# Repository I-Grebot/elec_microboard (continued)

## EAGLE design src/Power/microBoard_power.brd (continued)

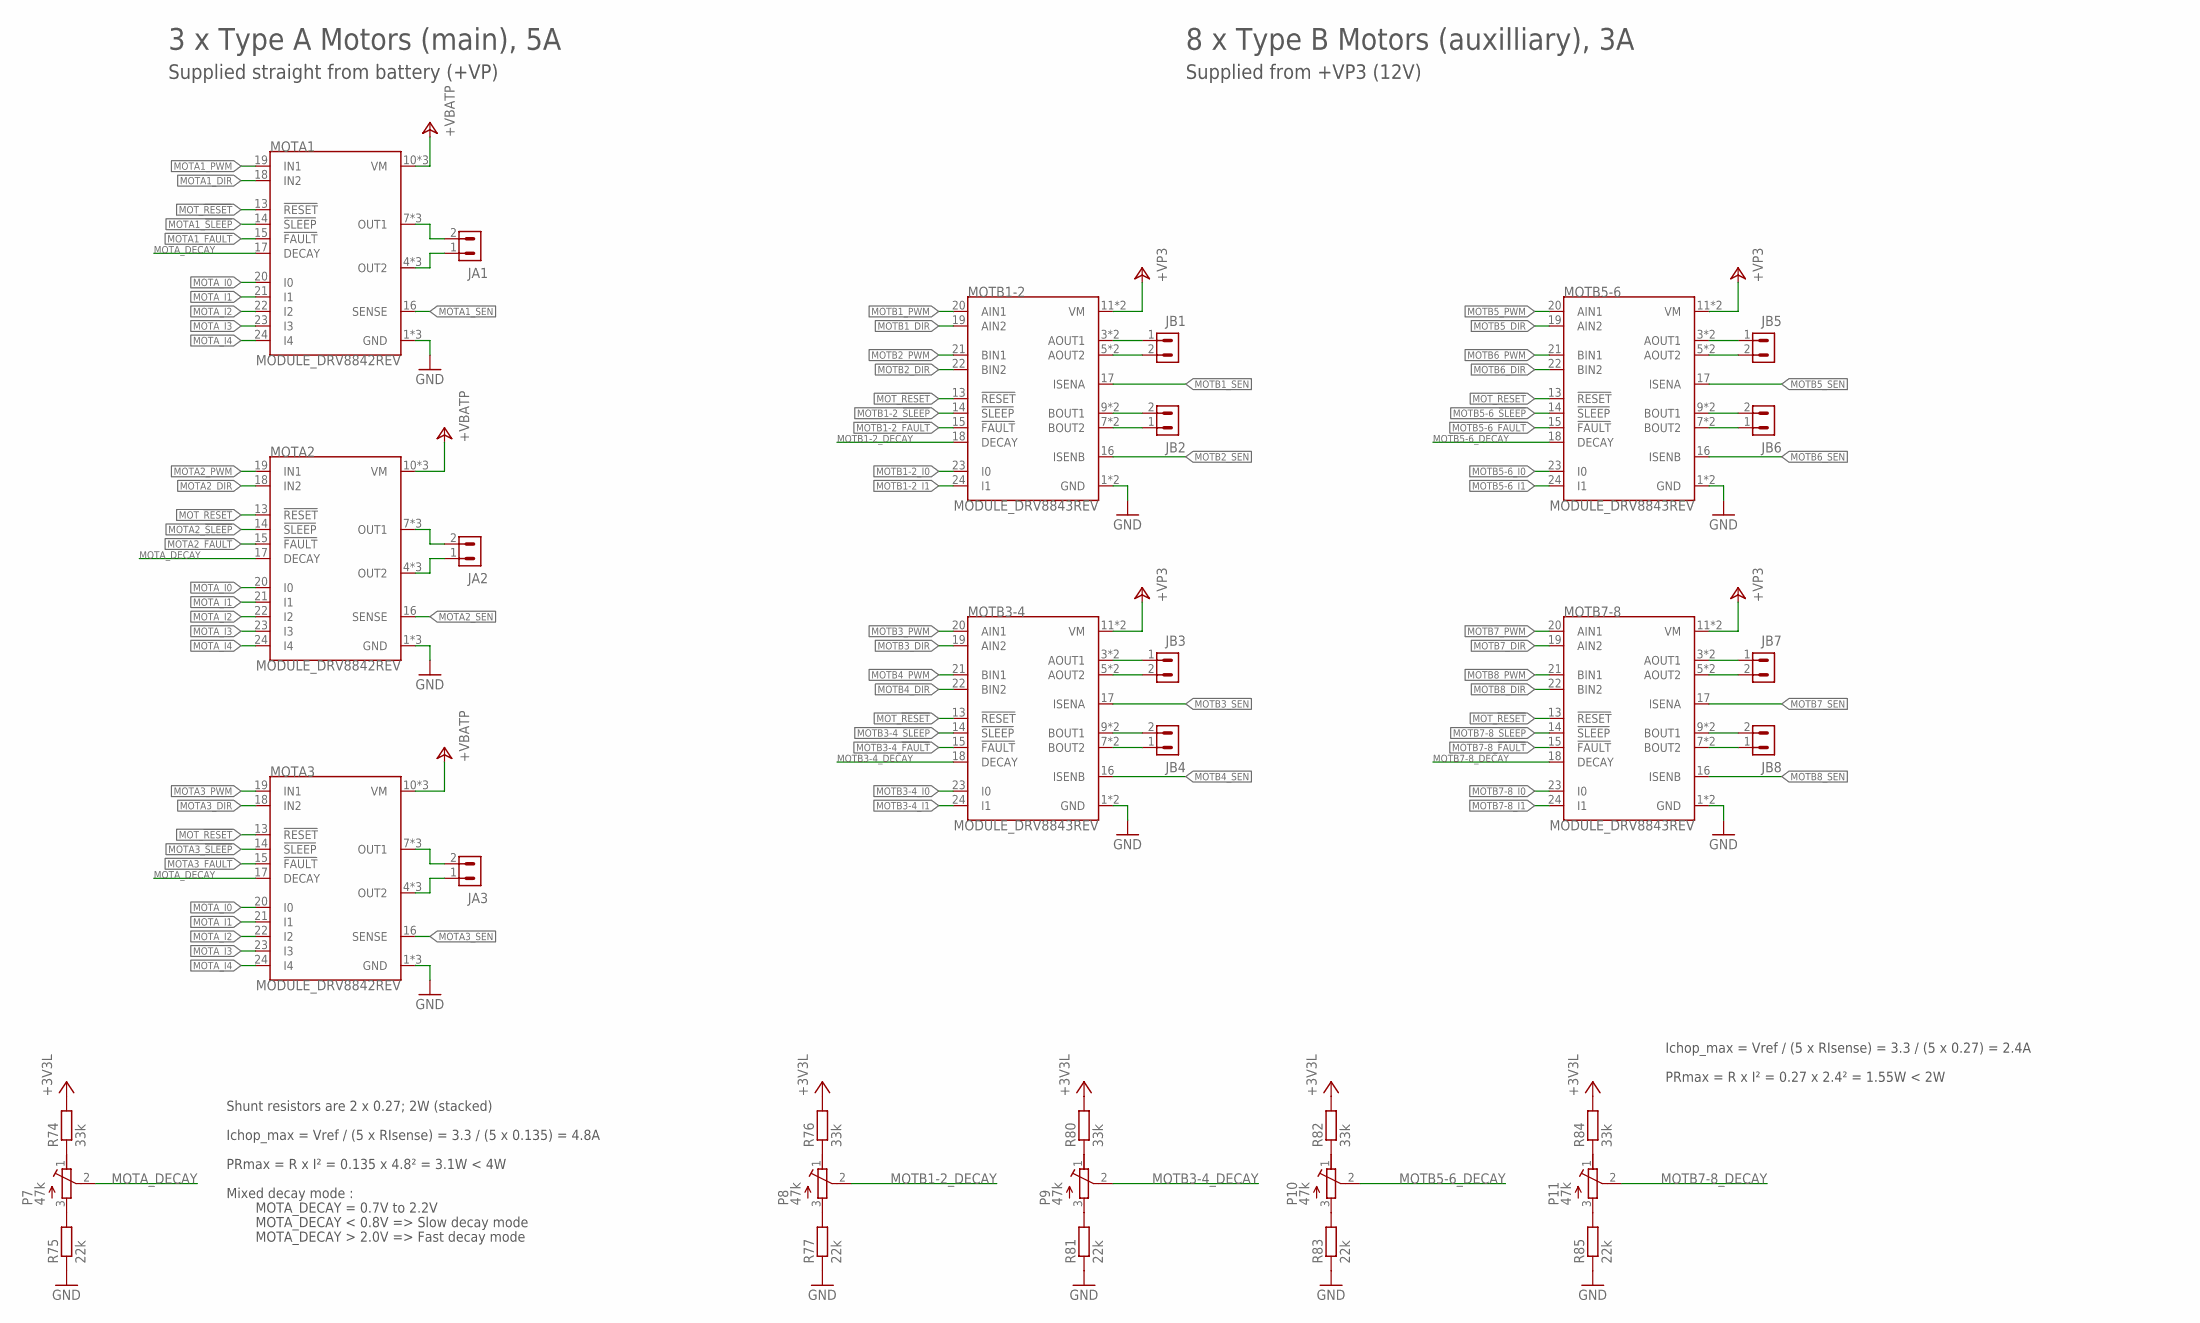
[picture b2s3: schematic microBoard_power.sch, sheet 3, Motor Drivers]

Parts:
JA1, JA2, JA3: MC15-G-3-3.81_2; CON_3.81_2
JB1, JB2, JB3, JB4, JB5, JB6, JB7, JB8: MC15-G-3-3.81_2; CON_3.81_2
MOTA1, MOTA2, MOTA3: MODULE_DRV8842REV; MODULE_DRV884X_REV
MOTB1-2, MOTB3-4, MOTB5-6, MOTB7-8: MODULE_DRV8843REV; MODULE_DRV884X_REV
P7, P8, P9, P10, P11: 47k; RTRIMT93XB
R74, R76, R80, R82, R84: 33k; R0603
R75, R77, R81, R83, R85: 22k; R0603

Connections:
+3V3L: R74.2, R76.2, R80.2, R82.2, R84.2; also elsewhere on the board
+VBATP: MOTA1.10 (VM), MOTA1.11 (VM), MOTA1.12 (VM), MOTA2.10 (VM), MOTA2.11 (VM), MOTA2.12 (VM), MOTA3.10 (VM), MOTA3.11 (VM), MOTA3.12 (VM); also elsewhere on the board
+VP3: MOTB1-2.11 (VM), MOTB1-2.12 (VM), MOTB3-4.11 (VM), MOTB3-4.12 (VM), MOTB5-6.11 (VM), MOTB5-6.12 (VM), MOTB7-8.11 (VM), MOTB7-8.12 (VM); also elsewhere on the board
GND: MOTA1.1 (GND), MOTA1.2 (GND), MOTA1.3 (GND), MOTA2.1 (GND), MOTA2.2 (GND), MOTA2.3 (GND), MOTA3.1 (GND), MOTA3.2 (GND), MOTA3.3 (GND), MOTB1-2.1 (GND), MOTB1-2.2 (GND), MOTB3-4.1 (GND), MOTB3-4.2 (GND), MOTB5-6.1 (GND), MOTB5-6.2 (GND), MOTB7-8.1 (GND), MOTB7-8.2 (GND), R75.1, R77.1, R81.1, R83.1, R85.1; also elsewhere on the board
MOTA1_!FAULT!: MOTA1.15 (!FAULT!); also elsewhere on the board
MOTA1_!SLEEP!: MOTA1.14 (!SLEEP!); also elsewhere on the board
MOTA1_DIR: MOTA1.18 (IN2); also elsewhere on the board
MOTA1_PWM: MOTA1.19 (IN1); also elsewhere on the board
MOTA1_SEN: MOTA1.16 (SENSE); also elsewhere on the board
MOTA2_!FAULT!: MOTA2.15 (!FAULT!); also elsewhere on the board
MOTA2_!SLEEP!: MOTA2.14 (!SLEEP!); also elsewhere on the board
MOTA2_DIR: MOTA2.18 (IN2); also elsewhere on the board
MOTA2_PWM: MOTA2.19 (IN1); also elsewhere on the board
MOTA2_SEN: MOTA2.16 (SENSE); also elsewhere on the board
MOTA3_!FAULT!: MOTA3.15 (!FAULT!); also elsewhere on the board
MOTA3_!SLEEP!: MOTA3.14 (!SLEEP!); also elsewhere on the board
MOTA3_DIR: MOTA3.18 (IN2); also elsewhere on the board
MOTA3_PWM: MOTA3.19 (IN1); also elsewhere on the board
MOTA3_SEN: MOTA3.16 (SENSE); also elsewhere on the board
MOTA_DECAY: MOTA1.17 (DECAY), MOTA2.17 (DECAY), MOTA3.17 (DECAY), P7.2 (S)
MOTA_I0: MOTA1.20 (I0), MOTA2.20 (I0), MOTA3.20 (I0); also elsewhere on the board
MOTA_I1: MOTA1.21 (I1), MOTA2.21 (I1), MOTA3.21 (I1); also elsewhere on the board
MOTA_I2: MOTA1.22 (I2), MOTA2.22 (I2), MOTA3.22 (I2); also elsewhere on the board
MOTA_I3: MOTA1.23 (I3), MOTA2.23 (I3), MOTA3.23 (I3); also elsewhere on the board
MOTA_I4: MOTA1.24 (I4), MOTA2.24 (I4), MOTA3.24 (I4); also elsewhere on the board
MOTB1-2_!FAULT!: MOTB1-2.15 (!FAULT!); also elsewhere on the board
MOTB1-2_!SLEEP!: MOTB1-2.14 (!SLEEP!); also elsewhere on the board
MOTB1-2_DECAY: MOTB1-2.18 (DECAY), P8.2 (S)
MOTB1-2_I0: MOTB1-2.23 (I0); also elsewhere on the board
MOTB1-2_I1: MOTB1-2.24 (I1); also elsewhere on the board
MOTB1_DIR: MOTB1-2.19 (AIN2); also elsewhere on the board
MOTB1_PWM: MOTB1-2.20 (AIN1); also elsewhere on the board
MOTB1_SEN: MOTB1-2.17 (ISENA); also elsewhere on the board
MOTB2_DIR: MOTB1-2.22 (BIN2); also elsewhere on the board
MOTB2_PWM: MOTB1-2.21 (BIN1); also elsewhere on the board
MOTB2_SEN: MOTB1-2.16 (ISENB); also elsewhere on the board
MOTB3-4_!FAULT!: MOTB3-4.15 (!FAULT!); also elsewhere on the board
MOTB3-4_!SLEEP!: MOTB3-4.14 (!SLEEP!); also elsewhere on the board
MOTB3-4_DECAY: MOTB3-4.18 (DECAY), P9.2 (S)
MOTB3-4_I0: MOTB3-4.23 (I0); also elsewhere on the board
MOTB3-4_I1: MOTB3-4.24 (I1); also elsewhere on the board
MOTB3_DIR: MOTB3-4.19 (AIN2); also elsewhere on the board
MOTB3_PWM: MOTB3-4.20 (AIN1); also elsewhere on the board
MOTB3_SEN: MOTB3-4.17 (ISENA); also elsewhere on the board
MOTB4_DIR: MOTB3-4.22 (BIN2); also elsewhere on the board
MOTB4_PWM: MOTB3-4.21 (BIN1); also elsewhere on the board
MOTB4_SEN: MOTB3-4.16 (ISENB); also elsewhere on the board
MOTB5-6_!FAULT!: MOTB5-6.15 (!FAULT!); also elsewhere on the board
MOTB5-6_!SLEEP!: MOTB5-6.14 (!SLEEP!); also elsewhere on the board
MOTB5-6_DECAY: MOTB5-6.18 (DECAY), P10.2 (S)
MOTB5-6_I0: MOTB5-6.23 (I0); also elsewhere on the board
MOTB5-6_I1: MOTB5-6.24 (I1); also elsewhere on the board
MOTB5_DIR: MOTB5-6.19 (AIN2); also elsewhere on the board
MOTB5_PWM: MOTB5-6.20 (AIN1); also elsewhere on the board
MOTB5_SEN: MOTB5-6.17 (ISENA); also elsewhere on the board
MOTB6_DIR: MOTB5-6.22 (BIN2); also elsewhere on the board
MOTB6_PWM: MOTB5-6.21 (BIN1); also elsewhere on the board
MOTB6_SEN: MOTB5-6.16 (ISENB); also elsewhere on the board
MOTB7-8_!FAULT!: MOTB7-8.15 (!FAULT!); also elsewhere on the board
MOTB7-8_!SLEEP!: MOTB7-8.14 (!SLEEP!); also elsewhere on the board
MOTB7-8_DECAY: MOTB7-8.18 (DECAY), P11.2 (S)
MOTB7-8_I0: MOTB7-8.23 (I0); also elsewhere on the board
MOTB7-8_I1: MOTB7-8.24 (I1); also elsewhere on the board
MOTB7_DIR: MOTB7-8.19 (AIN2); also elsewhere on the board
MOTB7_PWM: MOTB7-8.20 (AIN1); also elsewhere on the board
MOTB7_SEN: MOTB7-8.17 (ISENA); also elsewhere on the board
MOTB8_DIR: MOTB7-8.22 (BIN2); also elsewhere on the board
MOTB8_PWM: MOTB7-8.21 (BIN1); also elsewhere on the board
MOTB8_SEN: MOTB7-8.16 (ISENB); also elsewhere on the board
MOT_!RESET!: MOTA1.13 (!RESET!), MOTA2.13 (!RESET!), MOTA3.13 (!RESET!), MOTB1-2.13 (!RESET!), MOTB3-4.13 (!RESET!), MOTB5-6.13 (!RESET!), MOTB7-8.13 (!RESET!); also elsewhere on the board
unnamed: JA1.2, MOTA1.7 (OUT1), MOTA1.8 (OUT1), MOTA1.9 (OUT1)
unnamed: JA2.2, MOTA2.7 (OUT1), MOTA2.8 (OUT1), MOTA2.9 (OUT1)
unnamed: JB3.1, MOTB3-4.3 (AOUT1), MOTB3-4.4 (AOUT1)
unnamed: JB3.2, MOTB3-4.5 (AOUT2), MOTB3-4.6 (AOUT2)
unnamed: JB4.1, MOTB3-4.7 (BOUT2), MOTB3-4.8 (BOUT2)
unnamed: JA2.1, MOTA2.4 (OUT2), MOTA2.5 (OUT2), MOTA2.6 (OUT2)
unnamed: JA1.1, MOTA1.4 (OUT2), MOTA1.5 (OUT2), MOTA1.6 (OUT2)
unnamed: JB1.1, MOTB1-2.3 (AOUT1), MOTB1-2.4 (AOUT1)
unnamed: JB1.2, MOTB1-2.5 (AOUT2), MOTB1-2.6 (AOUT2)
unnamed: JB2.2, MOTB1-2.9 (BOUT1), MOTB1-2.10 (BOUT1)
unnamed: JA3.1, MOTA3.4 (OUT2), MOTA3.5 (OUT2), MOTA3.6 (OUT2)
unnamed: JA3.2, MOTA3.7 (OUT1), MOTA3.8 (OUT1), MOTA3.9 (OUT1)
unnamed: JB4.2, MOTB3-4.9 (BOUT1), MOTB3-4.10 (BOUT1)
unnamed: JB5.1, MOTB5-6.3 (AOUT1), MOTB5-6.4 (AOUT1)
unnamed: JB5.2, MOTB5-6.5 (AOUT2), MOTB5-6.6 (AOUT2)
unnamed: JB6.2, MOTB5-6.9 (BOUT1), MOTB5-6.10 (BOUT1)
unnamed: JB2.1, MOTB1-2.7 (BOUT2), MOTB1-2.8 (BOUT2)
unnamed: JB6.1, MOTB5-6.7 (BOUT2), MOTB5-6.8 (BOUT2)
unnamed: JB7.1, MOTB7-8.3 (AOUT1), MOTB7-8.4 (AOUT1)
unnamed: JB7.2, MOTB7-8.5 (AOUT2), MOTB7-8.6 (AOUT2)
unnamed: JB8.2, MOTB7-8.9 (BOUT1), MOTB7-8.10 (BOUT1)
unnamed: JB8.1, MOTB7-8.7 (BOUT2), MOTB7-8.8 (BOUT2)
unnamed: P7.3 (E), R75.2
unnamed: P7.1 (A), R74.1
unnamed: P8.3 (E), R77.2
unnamed: P8.1 (A), R76.1
unnamed: P9.3 (E), R81.2
unnamed: P9.1 (A), R80.1
unnamed: P10.3 (E), R83.2
unnamed: P10.1 (A), R82.1
unnamed: P11.3 (E), R85.2
unnamed: P11.1 (A), R84.1

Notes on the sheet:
3 x Type A Motors (main), 5A
Ichop_max = Vref / (5 x RIsense) = 3.3 / (5 x 0.135) = 4.8A
Ichop_max = Vref / (5 x RIsense) = 3.3 / (5 x 0.27) = 2.4A
PRmax = R x I² = 0.27 x 2.4² = 1.55W < 2W
PRmax = R x I² = 0.135 x 4.8² = 3.1W < 4W
Shunt resistors are 2 x 0.27; 2W (stacked)
8 x Type B Motors (auxilliary), 3A
Supplied straight from battery (+VP)
Supplied from +VP3 (12V)
Mixed decay mode :
MOTA_DECAY = 0.7V to 2.2V
MOTA_DECAY < 0.8V => Slow decay mode
MOTA_DECAY > 2.0V => Fast decay mode

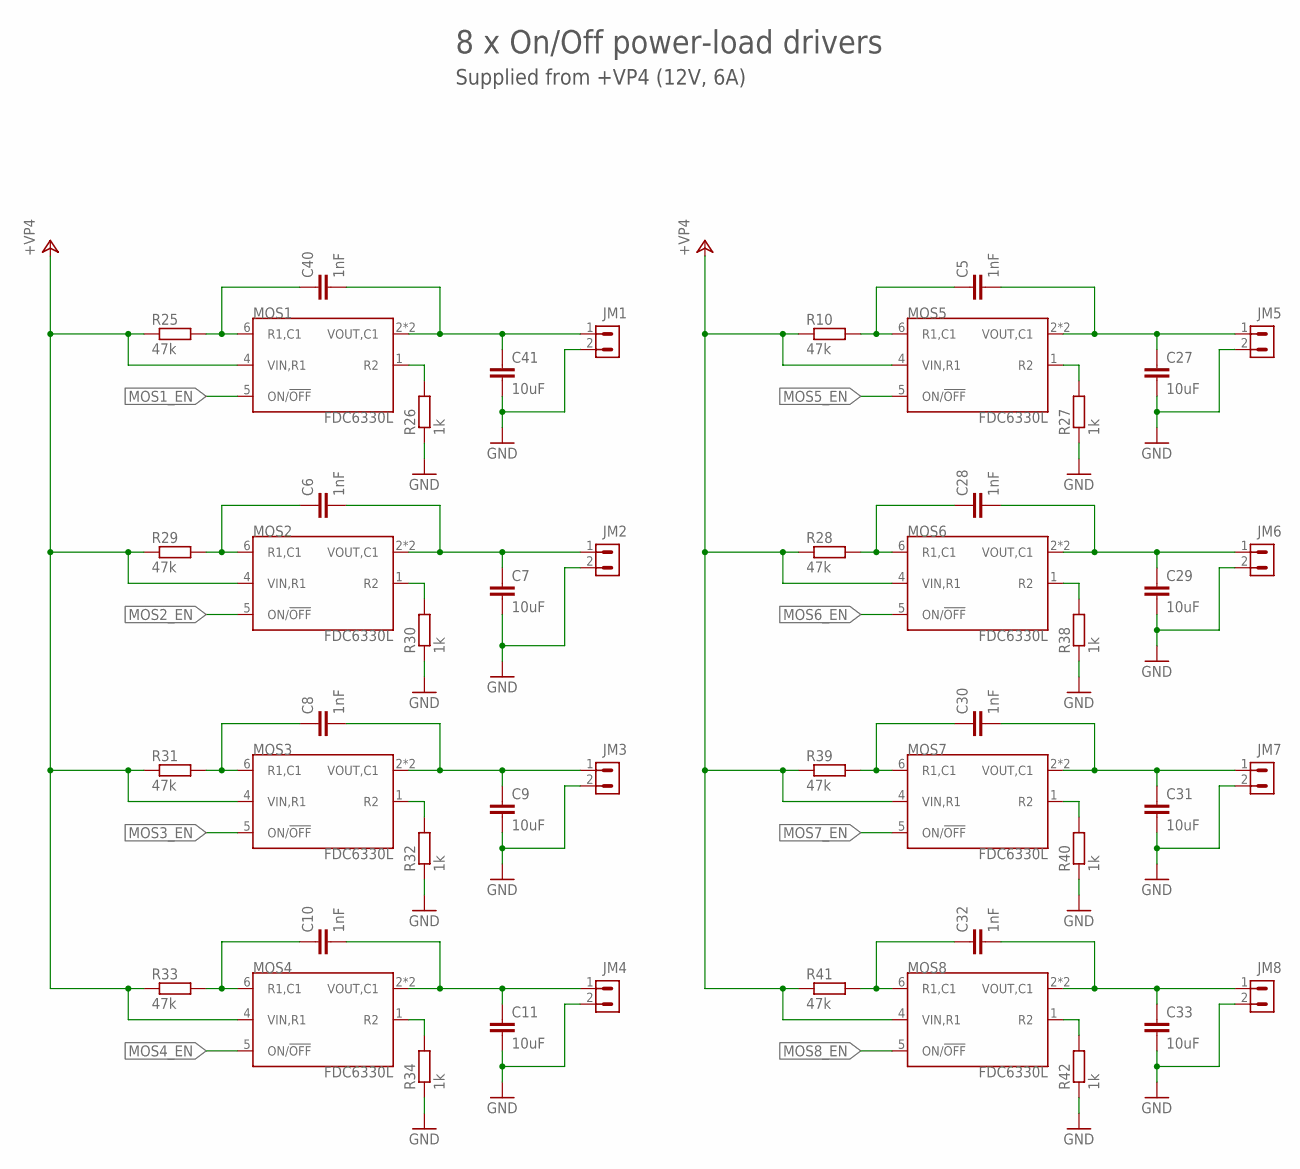
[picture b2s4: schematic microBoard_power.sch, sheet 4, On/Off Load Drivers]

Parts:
C5, C6, C8, C10, C28, C30, C32, C40: 1nF; C0603
C7, C9, C11, C27, C29, C31, C33, C41: 10uF; C1210
JM1, JM2, JM3, JM4, JM5, JM6, JM7, JM8: CON_2.54_H_2
MOS1, MOS2, MOS3, MOS4, MOS5, MOS6, MOS7, MOS8: FDC6330L; SSOT-6
R10, R25, R28, R29, R31, R33, R39, R41: 47k; R0603
R26, R27, R30, R32, R34, R38, R40, R42: 1k; R0603

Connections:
+VP4: MOS1.4 (VIN,R1), MOS2.4 (VIN,R1), MOS3.4 (VIN,R1), MOS4.4 (VIN,R1), MOS5.4 (VIN,R1), MOS6.4 (VIN,R1), MOS7.4 (VIN,R1), MOS8.4 (VIN,R1), R10.1, R25.1, R28.1, R29.1, R31.1, R33.1, R39.1, R41.1; also elsewhere on the board
GND: C7.2, C9.2, C11.2, C27.2, C29.2, C31.2, C33.2, C41.2, JM1.2, JM2.2, JM3.2, JM4.2, JM5.2, JM6.2, JM7.2, JM8.2, R26.1, R27.1, R30.1, R32.1, R34.1, R38.1, R40.1, R42.1; also elsewhere on the board
MOS1_EN: MOS1.5 (ON/!OFF!); also elsewhere on the board
MOS1_OUT: C40.2, C41.1, JM1.1, MOS1.2 (VOUT,C1), MOS1.3 (VOUT,C1)
MOS2_EN: MOS2.5 (ON/!OFF!); also elsewhere on the board
MOS2_OUT: C6.2, C7.1, JM2.1, MOS2.2 (VOUT,C1), MOS2.3 (VOUT,C1)
MOS3_EN: MOS3.5 (ON/!OFF!); also elsewhere on the board
MOS3_OUT: C8.2, C9.1, JM3.1, MOS3.2 (VOUT,C1), MOS3.3 (VOUT,C1)
MOS4_EN: MOS4.5 (ON/!OFF!); also elsewhere on the board
MOS4_OUT: C10.2, C11.1, JM4.1, MOS4.2 (VOUT,C1), MOS4.3 (VOUT,C1)
MOS5_EN: MOS5.5 (ON/!OFF!); also elsewhere on the board
MOS5_OUT: C5.2, C27.1, JM5.1, MOS5.2 (VOUT,C1), MOS5.3 (VOUT,C1)
MOS6_EN: MOS6.5 (ON/!OFF!); also elsewhere on the board
MOS6_OUT: C28.2, C29.1, JM6.1, MOS6.2 (VOUT,C1), MOS6.3 (VOUT,C1)
MOS7_EN: MOS7.5 (ON/!OFF!); also elsewhere on the board
MOS7_OUT: C30.2, C31.1, JM7.1, MOS7.2 (VOUT,C1), MOS7.3 (VOUT,C1)
MOS8_EN: MOS8.5 (ON/!OFF!); also elsewhere on the board
MOS8_OUT: C32.2, C33.1, JM8.1, MOS8.2 (VOUT,C1), MOS8.3 (VOUT,C1)
unnamed: MOS1.1 (R2), R26.2
unnamed: C5.1, MOS5.6 (R1,C1), R10.2
unnamed: C40.1, MOS1.6 (R1,C1), R25.2
unnamed: MOS5.1 (R2), R27.2
unnamed: C28.1, MOS6.6 (R1,C1), R28.2
unnamed: MOS6.1 (R2), R38.2
unnamed: C6.1, MOS2.6 (R1,C1), R29.2
unnamed: MOS2.1 (R2), R30.2
unnamed: C8.1, MOS3.6 (R1,C1), R31.2
unnamed: MOS3.1 (R2), R32.2
unnamed: C10.1, MOS4.6 (R1,C1), R33.2
unnamed: MOS4.1 (R2), R34.2
unnamed: C30.1, MOS7.6 (R1,C1), R39.2
unnamed: MOS7.1 (R2), R40.2
unnamed: C32.1, MOS8.6 (R1,C1), R41.2
unnamed: MOS8.1 (R2), R42.2

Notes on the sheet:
8 x On/Off power-load drivers
Supplied from +VP4 (12V, 6A)

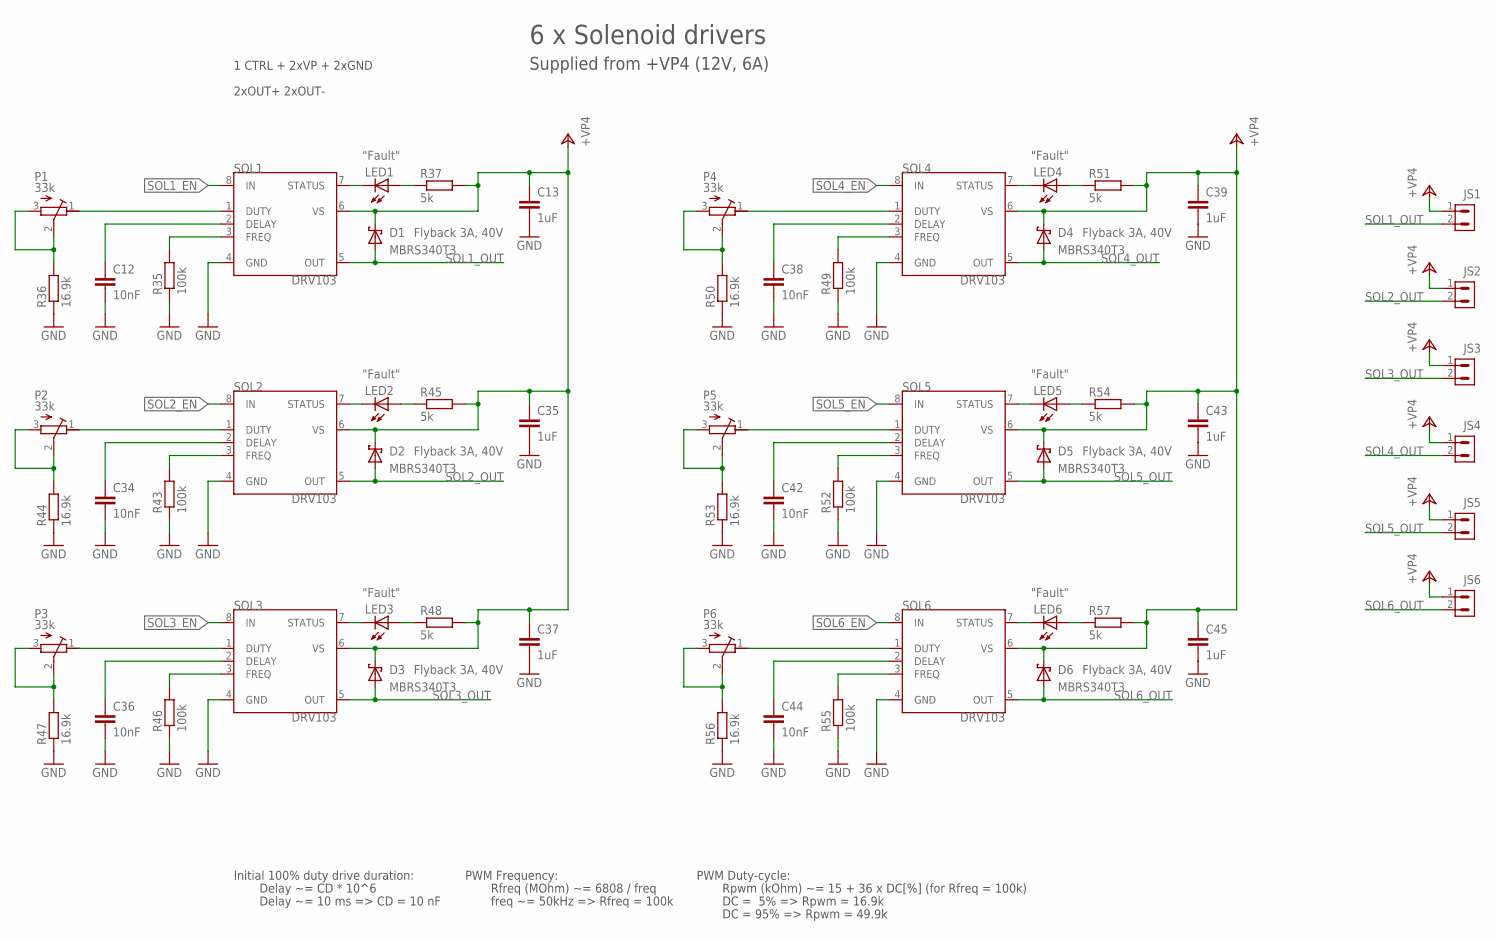
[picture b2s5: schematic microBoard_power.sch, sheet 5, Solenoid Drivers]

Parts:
C12, C34, C36, C38, C42, C44: 10nF; C0603
C13, C35, C37, C39, C43, C45: 1uF; C1210
D1, D2, D3, D4, D5, D6: MBRS340T3; SMC
JS1, JS2, JS3, JS4, JS5, JS6: CON_2.54_H_2
LED1, LED2, LED3, LED4, LED5, LED6: LEDCHIPLED_0805; CHIPLED_0805
P1, P2, P3, P4, P5, P6: 33k; RTRIMT93XB
R35, R43, R46, R49, R52, R55: 100k; R0603
R36, R44, R47, R50, R53, R56: 16.9k; R0603
R37, R45, R48, R51, R54, R57: 5k; R0603
SOL1, SOL2, SOL3, SOL4, SOL5, SOL6: DRV103; PWP_8

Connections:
+VP4: C13.1, C35.1, C37.1, C39.1, C43.1, C45.1, D1.C, D2.C, D3.C, D4.C, D5.C, D6.C, JS1.1, JS2.1, JS3.1, JS4.1, JS5.1, JS6.1, R37.2, R45.2, R48.2, R51.2, R54.2, R57.2, SOL1.6 (VS), SOL2.6 (VS), SOL3.6 (VS), SOL4.6 (VS), SOL5.6 (VS), SOL6.6 (VS); also elsewhere on the board
GND: C12.2, C13.2, C34.2, C35.2, C36.2, C37.2, C38.2, C39.2, C42.2, C43.2, C44.2, C45.2, R35.1, R36.1, R43.1, R44.1, R46.1, R47.1, R49.1, R50.1, R52.1, R53.1, R55.1, R56.1, SOL1.4 (GND), SOL2.4 (GND), SOL3.4 (GND), SOL4.4 (GND), SOL5.4 (GND), SOL6.4 (GND); also elsewhere on the board
unnamed: C38.1, SOL4.2 (DELAY)
unnamed: C34.1, SOL2.2 (DELAY)
unnamed: R43.2, SOL2.3 (FREQ)
unnamed: P2.1 (A), SOL2.1 (DUTY)
unnamed: P2.2 (S), P2.3 (E), R44.2
unnamed: LED2.C, SOL2.7 (STATUS)
unnamed: C12.1, SOL1.2 (DELAY)
unnamed: R35.2, SOL1.3 (FREQ)
unnamed: P1.1 (A), SOL1.1 (DUTY)
unnamed: P1.2 (S), P1.3 (E), R36.2
unnamed: LED1.C, SOL1.7 (STATUS)
unnamed: LED1.A, R37.1
unnamed: LED2.A, R45.1
unnamed: R49.2, SOL4.3 (FREQ)
unnamed: C36.1, SOL3.2 (DELAY)
unnamed: R46.2, SOL3.3 (FREQ)
unnamed: P3.1 (A), SOL3.1 (DUTY)
unnamed: P3.2 (S), P3.3 (E), R47.2
unnamed: LED3.C, SOL3.7 (STATUS)
unnamed: LED3.A, R48.1
unnamed: P4.1 (A), SOL4.1 (DUTY)
unnamed: P4.2 (S), P4.3 (E), R50.2
unnamed: LED4.C, SOL4.7 (STATUS)
unnamed: LED4.A, R51.1
unnamed: C42.1, SOL5.2 (DELAY)
unnamed: R52.2, SOL5.3 (FREQ)
unnamed: P5.1 (A), SOL5.1 (DUTY)
unnamed: P5.2 (S), P5.3 (E), R53.2
unnamed: LED5.C, SOL5.7 (STATUS)
unnamed: LED5.A, R54.1
unnamed: C44.1, SOL6.2 (DELAY)
unnamed: R55.2, SOL6.3 (FREQ)
unnamed: P6.1 (A), SOL6.1 (DUTY)
unnamed: P6.2 (S), P6.3 (E), R56.2
unnamed: LED6.C, SOL6.7 (STATUS)
unnamed: LED6.A, R57.1
SOL1_EN: SOL1.8 (IN); also elsewhere on the board
SOL1_OUT: D1.A, JS1.2, SOL1.5 (OUT)
SOL2_EN: SOL2.8 (IN); also elsewhere on the board
SOL2_OUT: D2.A, JS2.2, SOL2.5 (OUT)
SOL3_EN: SOL3.8 (IN); also elsewhere on the board
SOL3_OUT: D3.A, JS3.2, SOL3.5 (OUT)
SOL4_EN: SOL4.8 (IN); also elsewhere on the board
SOL4_OUT: D4.A, JS4.2, SOL4.5 (OUT)
SOL5_EN: SOL5.8 (IN); also elsewhere on the board
SOL5_OUT: D5.A, JS5.2, SOL5.5 (OUT)
SOL6_EN: SOL6.8 (IN); also elsewhere on the board
SOL6_OUT: D6.A, JS6.2, SOL6.5 (OUT)

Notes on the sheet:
Initial 100% duty drive duration:
Delay ~= CD * 10^6
Delay ~= 10 ms => CD = 10 nF
PWM Frequency:
Rfreq (MOhm) ~= 6808 / freq
freq ~= 50kHz => Rfreq = 100k
PWM Duty-cycle:
Rpwm (kOhm) ~= 15 + 36 x DC[%] (for Rfreq = 100k)
DC = 5% => Rpwm = 16.9k
DC = 95% => Rpwm = 49.9k
Flyback 3A, 40V
"Fault"
6 x Solenoid drivers
Supplied from +VP4 (12V, 6A)
1 CTRL + 2xVP + 2xGND
2xOUT+ 2xOUT-

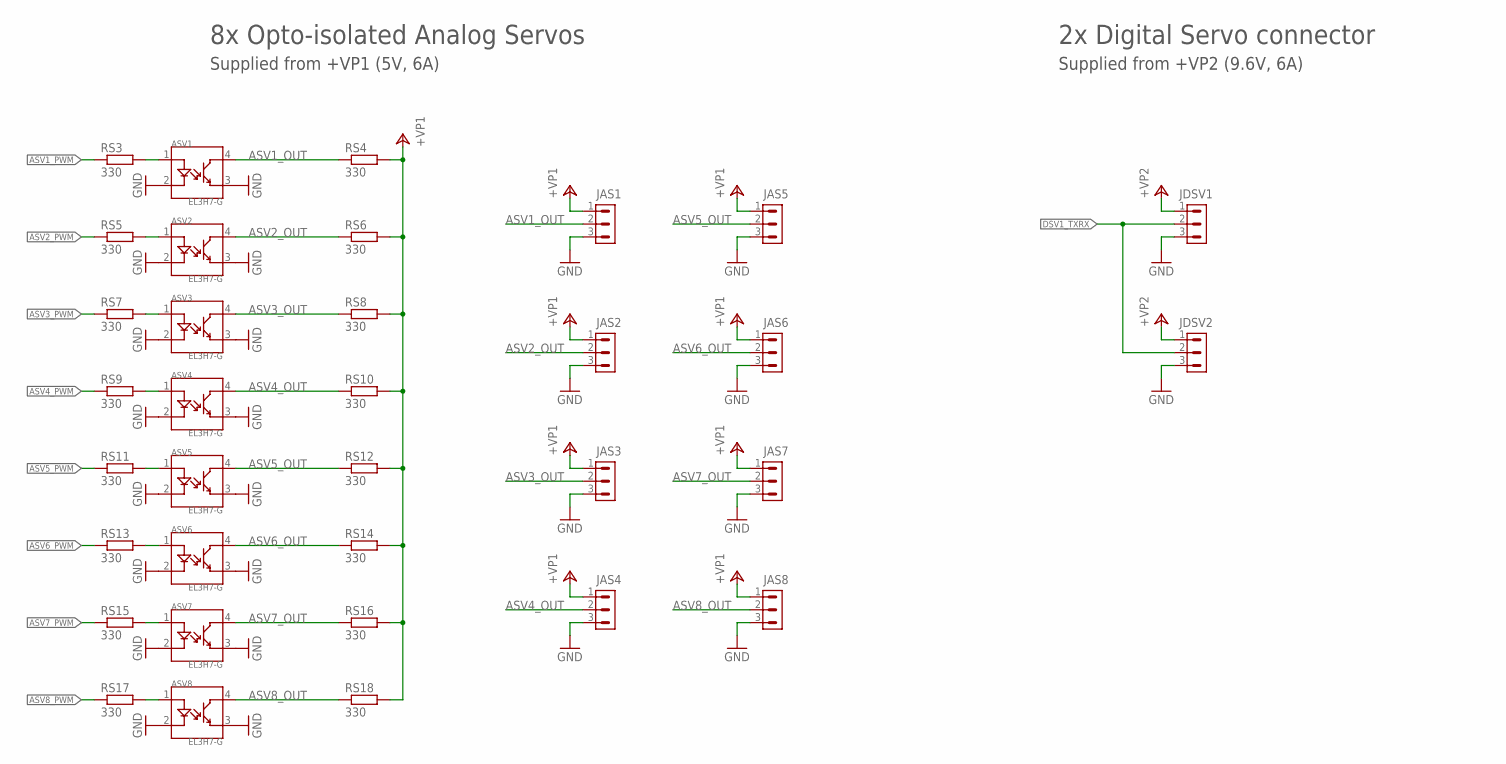
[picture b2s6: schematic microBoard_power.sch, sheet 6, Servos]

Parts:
ASV1, ASV2, ASV3, ASV4, ASV5, ASV6, ASV7, ASV8: EL3H7-G; SSOP_4
JAS1, JAS2, JAS3, JAS4, JAS5, JAS6, JAS7, JAS8: HE14_H_3
JDSV1, JDSV2: HE14_H_3
RS3, RS4, RS5, RS6, RS7, RS8, RS9, RS10, RS11, RS12, RS13, RS14, RS15, RS16, RS17, RS18: 330; R0603

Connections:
+VP1: JAS1.1, JAS2.1, JAS3.1, JAS4.1, JAS5.1, JAS6.1, JAS7.1, JAS8.1, RS4.2, RS6.2, RS8.2, RS10.2, RS12.2, RS14.2, RS16.2, RS18.2; also elsewhere on the board
+VP2: JDSV1.1, JDSV2.1; also elsewhere on the board
ASV1_OUT: ASV1.4, JAS1.2, RS4.1
ASV1_PWM: RS3.1; also elsewhere on the board
ASV2_OUT: ASV2.4, JAS2.2, RS6.1
ASV2_PWM: RS5.1; also elsewhere on the board
ASV3_OUT: ASV3.4, JAS3.2, RS8.1
ASV3_PWM: RS7.1; also elsewhere on the board
ASV4_OUT: ASV4.4, JAS4.2, RS10.1
ASV4_PWM: RS9.1; also elsewhere on the board
ASV5_OUT: ASV5.4, JAS5.2, RS12.1
ASV5_PWM: RS11.1; also elsewhere on the board
ASV6_OUT: ASV6.4, JAS6.2, RS14.1
ASV6_PWM: RS13.1; also elsewhere on the board
ASV7_OUT: ASV7.4, JAS7.2, RS16.1
ASV7_PWM: RS15.1; also elsewhere on the board
ASV8_OUT: ASV8.4, JAS8.2, RS18.1
ASV8_PWM: RS17.1; also elsewhere on the board
DSV1_TXRX: JDSV1.2, JDSV2.2; also elsewhere on the board
GND: ASV1.2, ASV1.3, ASV2.2, ASV2.3, ASV3.2, ASV3.3, ASV4.2, ASV4.3, ASV5.2, ASV5.3, ASV6.2, ASV6.3, ASV7.2, ASV7.3, ASV8.2, ASV8.3, JAS1.3, JAS2.3, JAS3.3, JAS4.3, JAS5.3, JAS6.3, JAS7.3, JAS8.3, JDSV1.3, JDSV2.3; also elsewhere on the board
unnamed: ASV1.1, RS3.2
unnamed: ASV2.1, RS5.2
unnamed: ASV3.1, RS7.2
unnamed: ASV4.1, RS9.2
unnamed: ASV5.1, RS11.2
unnamed: ASV6.1, RS13.2
unnamed: ASV7.1, RS15.2
unnamed: ASV8.1, RS17.2

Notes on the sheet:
8x Opto-isolated Analog Servos
Supplied from +VP1 (5V, 6A)
2x Digital Servo connector
Supplied from +VP2 (9.6V, 6A)

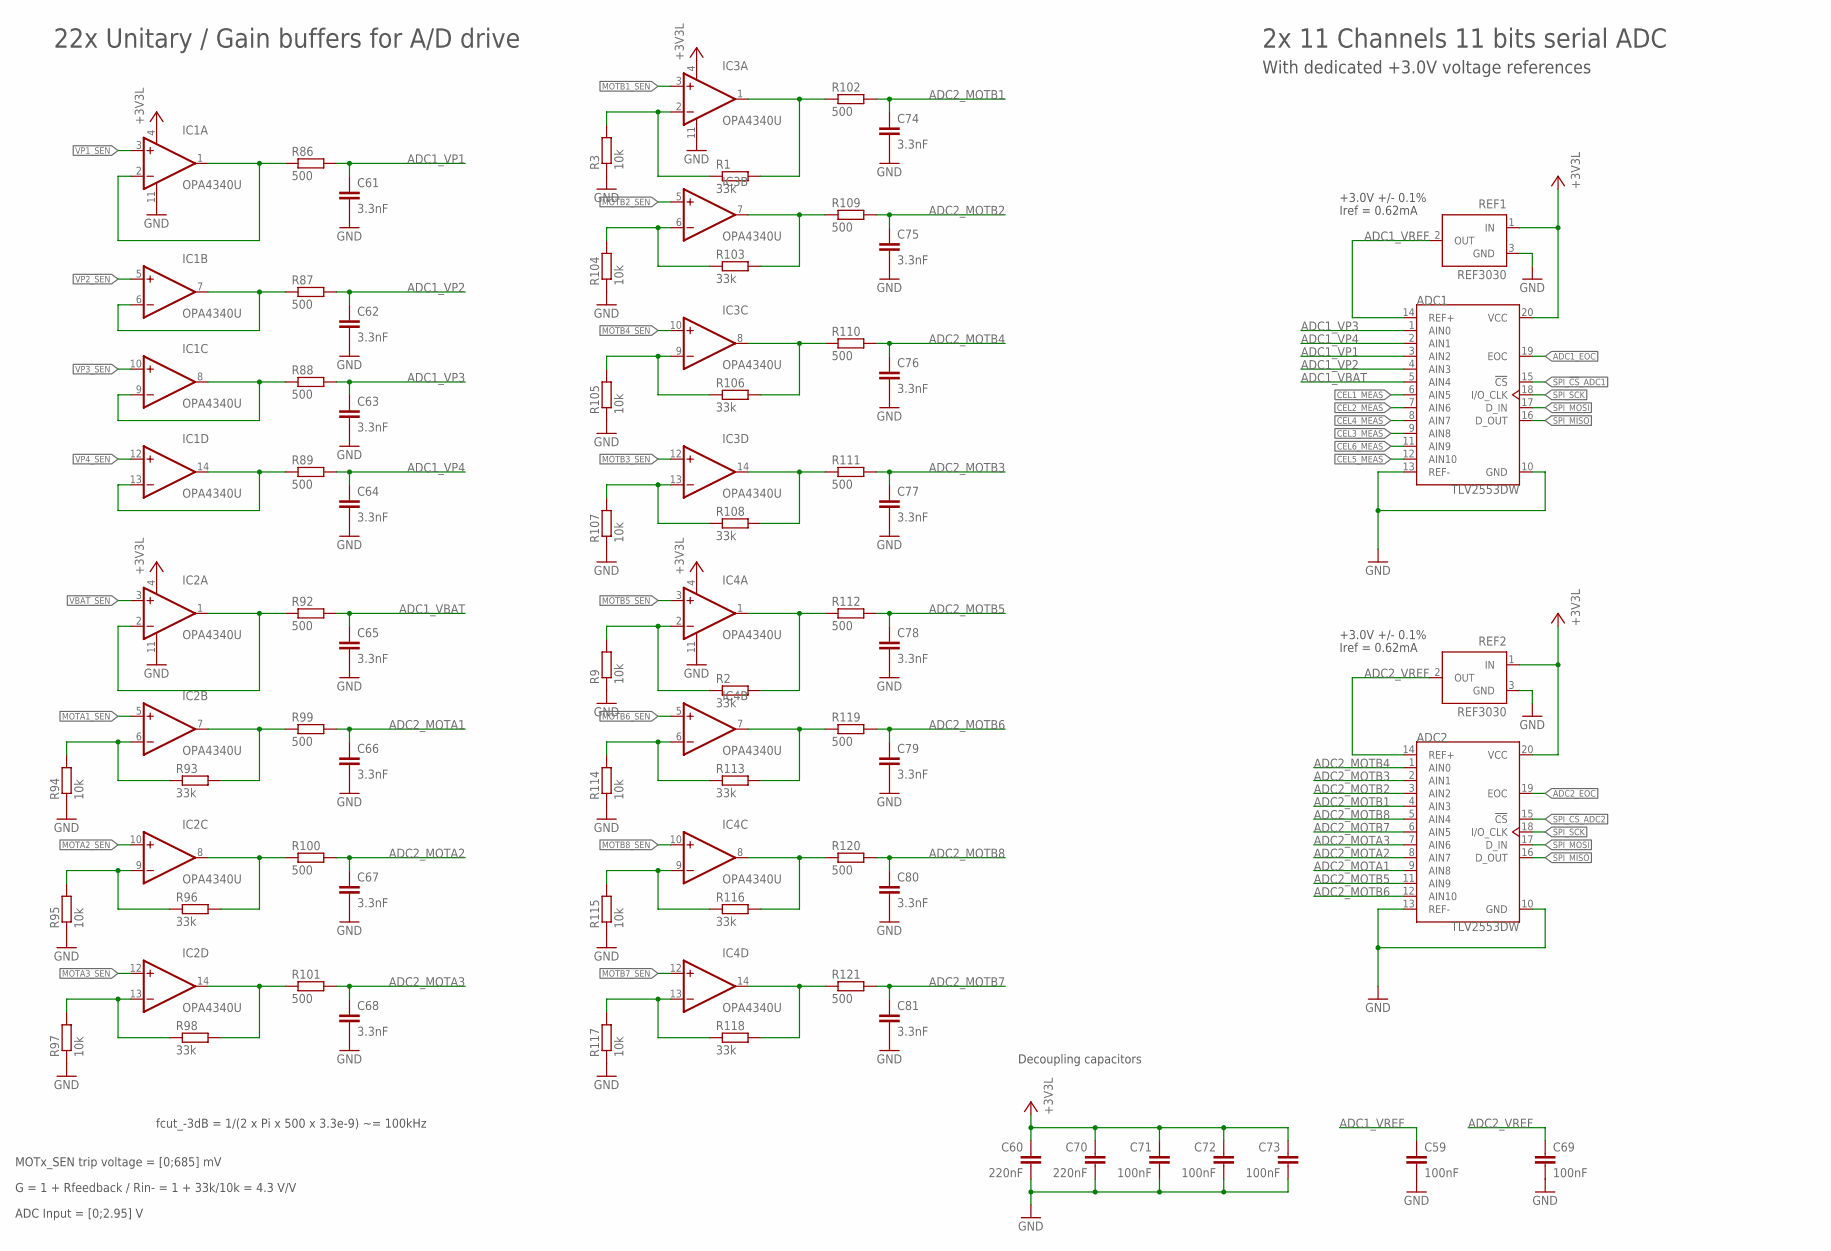
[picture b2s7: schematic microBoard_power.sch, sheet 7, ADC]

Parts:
ADC1, ADC2: TLV2553DW; SSOP_20
C59, C69, C71, C72, C73: 100nF; C0603
C60, C70: 220nF; C0603
C61, C62, C63, C64, C65, C66, C67, C68, C74, C75, C76, C77, C78, C79, C80, C81: 3.3nF; C0603
IC1, IC2, IC3, IC4: OPA4340U; SO14
R1, R2, R93, R96, R98, R103, R106, R108, R113, R116, R118: 33k; R0603
R3, R9, R94, R95, R97, R104, R105, R107, R114, R115, R117: 10k; R0603
R86, R87, R88, R89, R92, R99, R100, R101, R102, R109, R110, R111, R112, R119, R120, R121: 500; R0603
REF1, REF2: REF3030; SOT23

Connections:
+3V3L: ADC1.20 (VCC), ADC2.20 (VCC), C60.1, C70.1, C71.1, C72.1, C73.1, IC1.4 (V+), IC2.4 (V+), IC3.4 (V+), IC4.4 (V+), REF1.1 (IN), REF2.1 (IN); also elsewhere on the board
ADC1_EOC: ADC1.19 (EOC); also elsewhere on the board
ADC1_VBAT: ADC1.5 (AIN4), C65.1, R92.2
ADC1_VP1: ADC1.3 (AIN2), C61.1, R86.2
ADC1_VP2: ADC1.4 (AIN3), C62.1, R87.2
ADC1_VP3: ADC1.1 (AIN0), C63.1, R88.2
ADC1_VP4: ADC1.2 (AIN1), C64.1, R89.2
ADC1_VREF: ADC1.14 (REF+), C59.1, REF1.2 (OUT)
ADC2_EOC: ADC2.19 (EOC); also elsewhere on the board
ADC2_MOTA1: ADC2.9 (AIN8), C66.1, R99.2
ADC2_MOTA2: ADC2.8 (AIN7), C67.1, R100.2
ADC2_MOTA3: ADC2.7 (AIN6), C68.1, R101.2
ADC2_MOTB1: ADC2.4 (AIN3), C74.1, R102.2
ADC2_MOTB2: ADC2.3 (AIN2), C75.1, R109.2
ADC2_MOTB3: ADC2.2 (AIN1), C77.1, R111.2
ADC2_MOTB4: ADC2.1 (AIN0), C76.1, R110.2
ADC2_MOTB5: ADC2.11 (AIN9), C78.1, R112.2
ADC2_MOTB6: ADC2.12 (AIN10), C79.1, R119.2
ADC2_MOTB7: ADC2.6 (AIN5), C81.1, R121.2
ADC2_MOTB8: ADC2.5 (AIN4), C80.1, R120.2
ADC2_VREF: ADC2.14 (REF+), C69.1, REF2.2 (OUT)
CEL1_MEAS: ADC1.6 (AIN5); also elsewhere on the board
CEL2_MEAS: ADC1.7 (AIN6); also elsewhere on the board
CEL3_MEAS: ADC1.9 (AIN8); also elsewhere on the board
CEL4_MEAS: ADC1.8 (AIN7); also elsewhere on the board
CEL5_MEAS: ADC1.12 (AIN10); also elsewhere on the board
CEL6_MEAS: ADC1.11 (AIN9); also elsewhere on the board
GND: ADC1.10 (GND), ADC1.13 (REF-), ADC2.10 (GND), ADC2.13 (REF-), C59.2, C60.2, C61.2, C62.2, C63.2, C64.2, C65.2, C66.2, C67.2, C68.2, C69.2, C70.2, C71.2, C72.2, C73.2, C74.2, C75.2, C76.2, C77.2, C78.2, C79.2, C80.2, C81.2, IC1.11 (V-), IC2.11 (V-), IC3.11 (V-), IC4.11 (V-), R3.1, R9.1, R94.1, R95.1, R97.1, R104.1, R105.1, R107.1, R114.1, R115.1, R117.1, REF1.3 (GND), REF2.3 (GND); also elsewhere on the board
MOTA1_SEN: IC2.5 (+IN); also elsewhere on the board
MOTA2_SEN: IC2.10 (+IN); also elsewhere on the board
MOTA3_SEN: IC2.12 (+IN); also elsewhere on the board
MOTB1_SEN: IC3.3 (+IN); also elsewhere on the board
MOTB2_SEN: IC3.5 (+IN); also elsewhere on the board
MOTB3_SEN: IC3.12 (+IN); also elsewhere on the board
MOTB4_SEN: IC3.10 (+IN); also elsewhere on the board
MOTB5_SEN: IC4.3 (+IN); also elsewhere on the board
MOTB6_SEN: IC4.5 (+IN); also elsewhere on the board
MOTB7_SEN: IC4.12 (+IN); also elsewhere on the board
MOTB8_SEN: IC4.10 (+IN); also elsewhere on the board
unnamed: IC3.2 (-IN), R1.1, R3.2
unnamed: IC4.2 (-IN), R2.1, R9.2
unnamed: IC1.6 (-IN), IC1.7 (OUT), R87.1
unnamed: IC1.8 (OUT), IC1.9 (-IN), R88.1
unnamed: IC1.13 (-IN), IC1.14 (OUT), R89.1
unnamed: IC1.1 (OUT), IC1.2 (-IN), R86.1
unnamed: IC2.1 (OUT), IC2.2 (-IN), R92.1
unnamed: IC2.7 (OUT), R93.2, R99.1
unnamed: IC2.8 (OUT), R96.2, R100.1
unnamed: IC2.14 (OUT), R98.2, R101.1
unnamed: IC2.6 (-IN), R93.1, R94.2
unnamed: IC2.9 (-IN), R95.2, R96.1
unnamed: IC2.13 (-IN), R97.2, R98.1
unnamed: IC3.1 (OUT), R1.2, R102.1
unnamed: IC3.7 (OUT), R103.2, R109.1
unnamed: IC3.8 (OUT), R106.2, R110.1
unnamed: IC3.14 (OUT), R108.2, R111.1
unnamed: IC3.6 (-IN), R103.1, R104.2
unnamed: IC3.9 (-IN), R105.2, R106.1
unnamed: IC3.13 (-IN), R107.2, R108.1
unnamed: IC4.1 (OUT), R2.2, R112.1
unnamed: IC4.7 (OUT), R113.2, R119.1
unnamed: IC4.8 (OUT), R116.2, R120.1
unnamed: IC4.14 (OUT), R118.2, R121.1
unnamed: IC4.6 (-IN), R113.1, R114.2
unnamed: IC4.9 (-IN), R115.2, R116.1
unnamed: IC4.13 (-IN), R117.2, R118.1
SPI_!CS!_ADC1: ADC1.15 (!CS!); also elsewhere on the board
SPI_!CS!_ADC2: ADC2.15 (!CS!); also elsewhere on the board
SPI_MISO: ADC1.16 (D_OUT), ADC2.16 (D_OUT); also elsewhere on the board
SPI_MOSI: ADC1.17 (D_IN), ADC2.17 (D_IN); also elsewhere on the board
SPI_SCK: ADC1.18 (I/O_CLK), ADC2.18 (I/O_CLK); also elsewhere on the board
VBAT_SEN: IC2.3 (+IN); also elsewhere on the board
VP1_SEN: IC1.3 (+IN); also elsewhere on the board
VP2_SEN: IC1.5 (+IN); also elsewhere on the board
VP3_SEN: IC1.10 (+IN); also elsewhere on the board
VP4_SEN: IC1.12 (+IN); also elsewhere on the board

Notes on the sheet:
+3.0V +/- 0.1%
Iref = 0.62mA
Decoupling capacitors
fcut_-3dB = 1/(2 x Pi x 500 x 3.3e-9) ~= 100kHz
G = 1 + Rfeedback / Rin- = 1 + 33k/10k = 4.3 V/V
MOTx_SEN trip voltage = [0;685] mV
ADC Input = [0;2.95] V
22x Unitary / Gain buffers for A/D drive
2x 11 Channels 11 bits serial ADC
With dedicated +3.0V voltage references
